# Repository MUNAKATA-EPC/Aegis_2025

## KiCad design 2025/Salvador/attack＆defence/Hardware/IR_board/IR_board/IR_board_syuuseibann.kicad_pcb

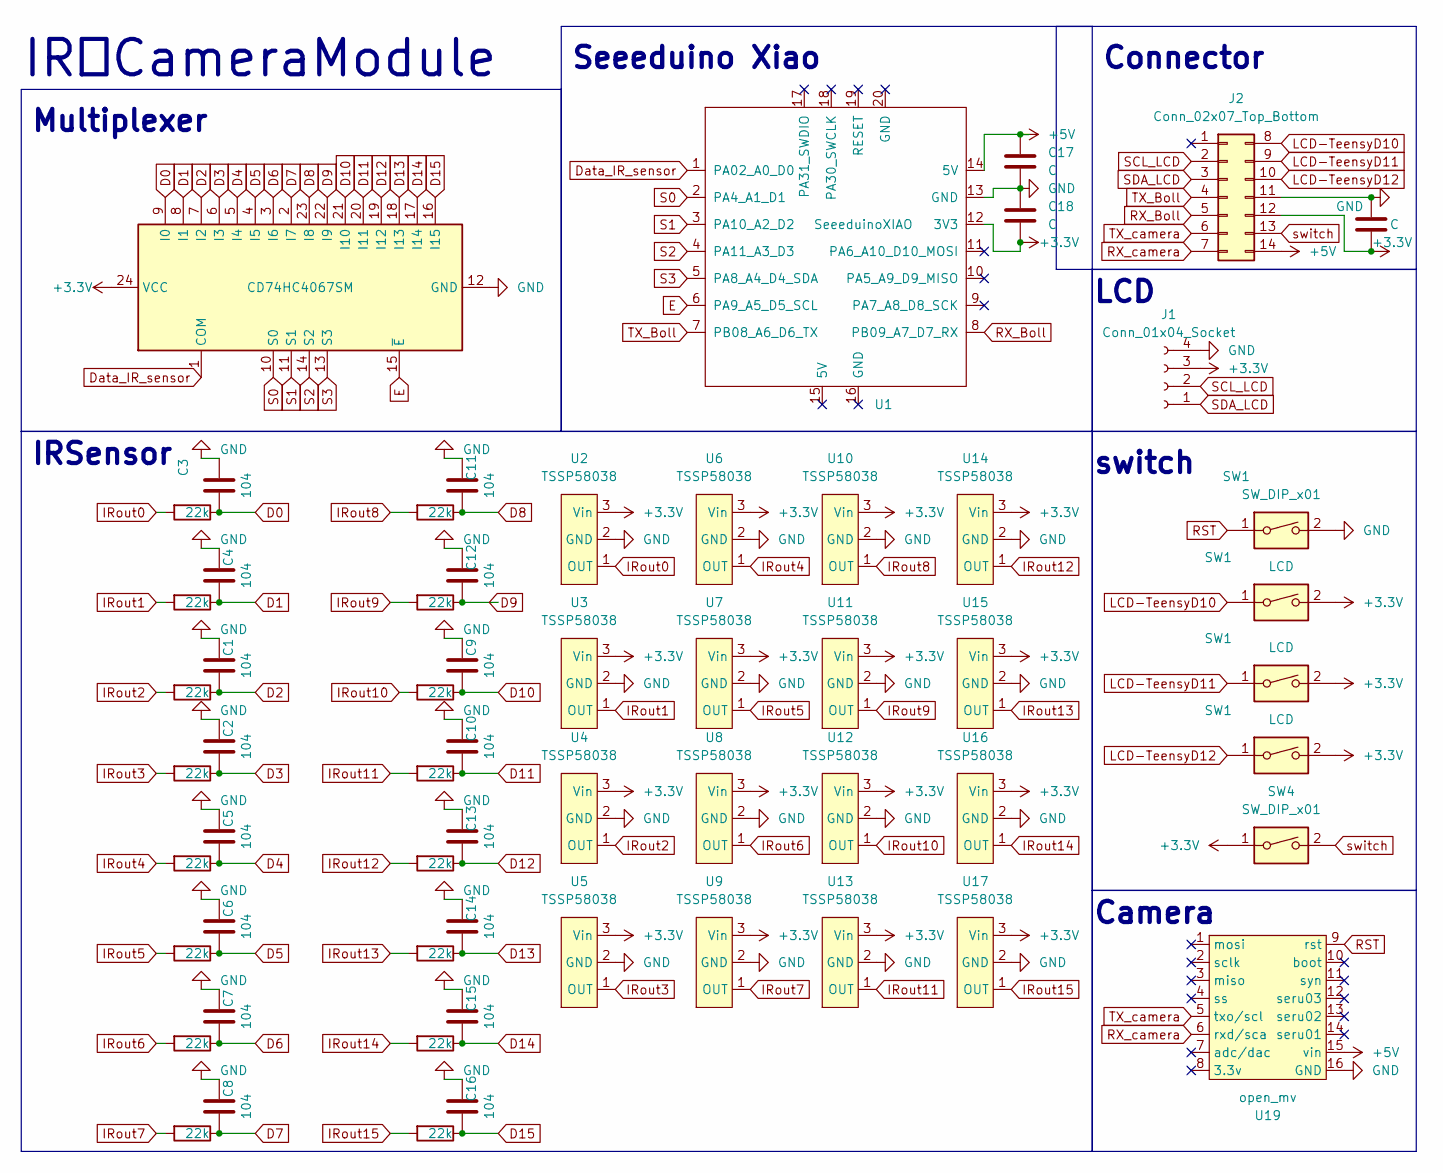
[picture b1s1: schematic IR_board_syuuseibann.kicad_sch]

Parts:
C1, C2, C3, C4, C5, C6, C7, C8, C9, C10, C11, C12, C13, C14, C15, C16: 104; C_Disc_D5.0mm_W2.5mm_P2.50mm
C17, C18, C19: C; C_Disc_D5.0mm_W2.5mm_P2.50mm
J1: Conn_01x04_Socket; PinHeader_1x04_P2.54mm_Vertical
J2: Conn_02x07_Top_Bottom; IDC-Header_2x07_P2.54mm_Vertical
R1, R2, R3, R4, R5, R6, R7, R8, R9, R10, R11, R12, R13, R14, R15, R16: 22k; R_Axial_DIN0204_L3.6mm_D1.6mm_P5.08mm_Vertical
SW1: LCD; SW_PUSH_6mm_H5mm
SW4: SW_DIP_x01; PinHeader_1x02_P2.54mm_Vertical
U1: SeeeduinoXIAO; seeeduinoXIAO
U2, U3, U4, U5, U6, U7, U8, U9, U10, U11, U12, U13, U14, U15, U16, U17: TSSP58038; PinHeader_1x03_P2.54mm_Vertical
U18: CD74HC4067SM; SSOP-24_5.3x8.2mm_P0.65mm
U19: open_mv; OpenMV

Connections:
+3.3V: C18.2, C19.2, J1.3, J2.12, SW1.2, SW4.1, U1.12 (3V3), U2.3 (Vin), U3.3 (Vin), U4.3 (Vin), U5.3 (Vin), U6.3 (Vin), U7.3 (Vin), U8.3 (Vin), U9.3 (Vin), U10.3 (Vin), U11.3 (Vin), U12.3 (Vin), U13.3 (Vin), U14.3 (Vin), U15.3 (Vin), U16.3 (Vin), U17.3 (Vin), U18.24 (VCC); also elsewhere on the board
+5V: C17.1, J2.14, U1.14 (5V), U19.15 (vin)
D0: C3.1, R3.1, U18.9 (I0)
D1: C4.1, R4.1, U18.8 (I1)
D2: C1.1, R1.1, U18.7 (I2)
D3: C2.1, R2.1, U18.6 (I3)
D4: C5.1, R5.1, U18.5 (I4)
D5: C6.1, R6.1, U18.4 (I5)
D6: C7.1, R7.1, U18.3 (I6)
D7: C8.1, R8.1, U18.2 (I7)
D8: C11.1, R11.1, U18.23 (I8)
D9: C12.1, R12.1, U18.22 (I9)
D10: C9.1, R9.1, U18.21 (I10)
D11: C10.1, R10.1, U18.20 (I11)
D12: C13.1, R13.1, U18.19 (I12)
D13: C14.1, R14.1, U18.18 (I13)
D14: C15.1, R15.1, U18.17 (I14)
D15: C16.1, R16.1, U18.16 (I15)
Data_IR_sensor: U1.1 (PA02_A0_D0), U18.1 (COM)
E: U1.6 (PA9_A5_D5_SCL), U18.15 (~E)
GND: C1.2, C2.2, C3.2, C4.2, C5.2, C6.2, C7.2, C8.2, C9.2, C10.2, C11.2, C12.2, C13.2, C14.2, C15.2, C16.2, C17.2, C18.1, C19.1, J1.4, J2.11, SW1.2, U1.13 (GND), U2.2 (GND), U3.2 (GND), U4.2 (GND), U5.2 (GND), U6.2 (GND), U7.2 (GND), U8.2 (GND), U9.2 (GND), U10.2 (GND), U11.2 (GND), U12.2 (GND), U13.2 (GND), U14.2 (GND), U15.2 (GND), U16.2 (GND), U17.2 (GND), U18.12 (GND), U19.16 (GND); also elsewhere on the board
IRout0: R3.2, U2.1 (OUT)
IRout1: R4.2, U3.1 (OUT)
IRout2: R1.2, U4.1 (OUT)
IRout3: R2.2, U5.1 (OUT)
IRout4: R5.2, U6.1 (OUT)
IRout5: R6.2, U7.1 (OUT)
IRout6: R7.2, U8.1 (OUT)
IRout7: R8.2, U9.1 (OUT)
IRout8: R11.2, U10.1 (OUT)
IRout9: R12.2, U11.1 (OUT)
IRout10: R9.2, U12.1 (OUT)
IRout11: R10.2, U13.1 (OUT)
IRout12: R13.2, U14.1 (OUT)
IRout13: R14.2, U15.1 (OUT)
IRout14: R15.2, U16.1 (OUT)
IRout15: R16.2, U17.1 (OUT)
LCD-TeensyD10: J2.8, SW1.1; also elsewhere on the board
LCD-TeensyD11: J2.9; also elsewhere on the board
LCD-TeensyD12: J2.10, SW1.1; also elsewhere on the board
RST: SW1.1, U19.9 (rst); also elsewhere on the board
RX_Boll: J2.5, U1.8 (PB09_A7_D7_RX)
RX_camera: J2.7, U19.6 (rxd/sca)
S0: U1.2 (PA4_A1_D1), U18.10 (S0)
S1: U1.3 (PA10_A2_D2), U18.11 (S1)
S2: U1.4 (PA11_A3_D3), U18.14 (S2)
S3: U1.5 (PA8_A4_D4_SDA), U18.13 (S3)
SCL_LCD: J1.2, J2.2
SDA_LCD: J1.1, J2.3
TX_Boll: J2.4, U1.7 (PB08_A6_D6_TX)
TX_camera: J2.6, U19.5 (txo/scl)
switch: J2.13, SW4.2

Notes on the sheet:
LCD
switch
Multiplexer
Camera
IRSensor
Connector
Seeeduino Xiao
IR＆CameraModule

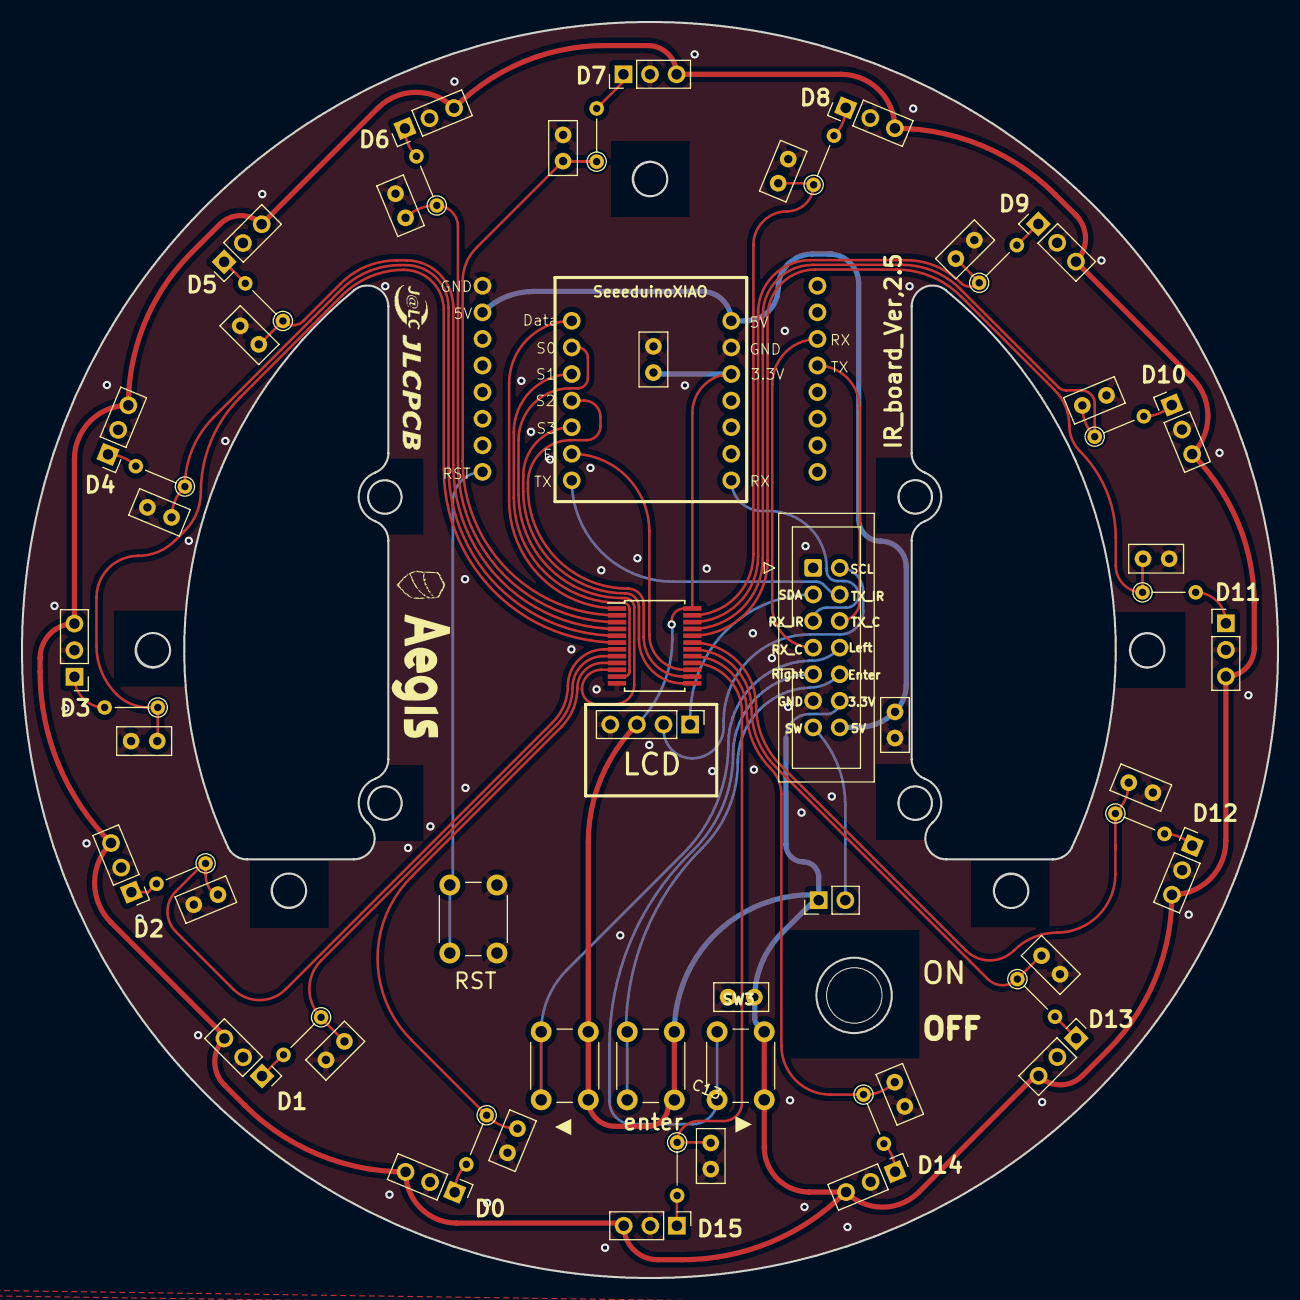
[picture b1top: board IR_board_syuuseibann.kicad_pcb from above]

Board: 2 copper layers, 120.0 x 120.0 mm, 61 parts (0 on the bottom side), 52 nets.

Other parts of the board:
RST: SW_DIP_x01; SW_PUSH_6mm_H5mm
SW3: LCD; SW_PUSH_6mm_H5mm
enter: LCD; SW_PUSH_6mm_H5mm
▶: LCD; SW_PUSH_6mm_H5mm

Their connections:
+3.3V: SW3.2, enter.2, ▶.2; also elsewhere on the board
GND: RST.2; also elsewhere on the board
LCD-TeensyD10: ▶.1; also elsewhere on the board
LCD-TeensyD11: SW3.1; also elsewhere on the board
LCD-TeensyD12: enter.1; also elsewhere on the board
RST: RST.1; also elsewhere on the board

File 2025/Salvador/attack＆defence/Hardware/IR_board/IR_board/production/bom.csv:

Designator,Footprint,Quantity,Value,LCSC Part #
"C1, C10, C11, C12, C13, C14, C15, C16, C2, C3, C4, C5, C6, C7, C8, C9",C_Disc_D5.0mm_W2.5mm_P2.50mm,16,104,
Camera_RST1,SW_PUSH_6mm_H5mm,1,SW_DIP_x01,
J1,PinHeader_1x04_P2.54mm_Vertical,1,Conn_01x04_Socket,
J2,IDC-Header_2x07_P2.54mm_Vertical,1,Conn_02x07_Top_Bottom,
"R1, R10, R11, R12, R13, R14, R15, R16, R2, R3, R4, R5, R6, R7, R8, R9",R_Axial_DIN0204_L3.6mm_D1.6mm_P5.08mm_Vertical,16,22k,
"SW1, SW2, SW3",SW_PUSH_6mm_H5mm,3,LCD,
SW4,PinHeader_1x02_P2.54mm_Vertical,1,SW_DIP_x01,
U1,seeeduinoXIAO,1,SeeeduinoXIAO,
"U10, U11, U12, U13, U14, U15, U16, U17, U2, U3, U4, U5, U6, U7, U8, U9",PinHeader_1x03_P2.54mm_Vertical,16,TSSP58038,
U18,SSOP-24_5.3x8.2mm_P0.65mm,1,CD74HC4067SM,
U19,OpenMV,1,open_mv,

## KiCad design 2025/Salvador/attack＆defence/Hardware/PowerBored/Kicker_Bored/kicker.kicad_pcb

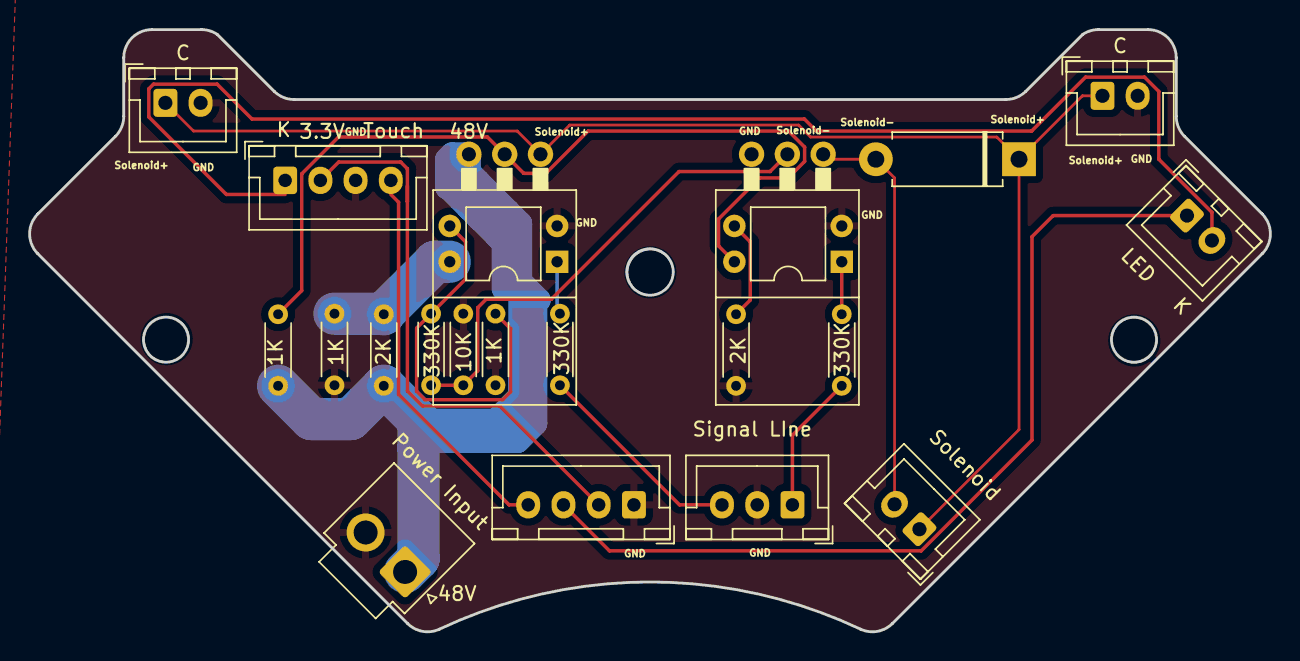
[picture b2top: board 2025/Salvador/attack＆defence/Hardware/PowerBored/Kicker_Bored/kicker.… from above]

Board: 2 copper layers, 88.1 x 42.7 mm, 22 parts (0 on the bottom side), 17 nets.

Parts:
1K, 1K#2: 1K; R_Axial_DIN0204_L3.6mm_D1.6mm_P5.08mm_Horizontal
2K, 2K#2: 2K; R_Axial_DIN0204_L3.6mm_D1.6mm_P5.08mm_Horizontal
330K, 330K#2: 330K; R_Axial_DIN0204_L3.6mm_D1.6mm_P5.08mm_Horizontal
C: C; JST_XH_B2B-XH-A_1x02_P2.50mm_Vertical
C#2: C; JST_XH_B2B-XH-A_1x02_P2.50mm_Vertical
D1: D; D_DO-15_P10.16mm_Horizontal
J1: Conn_01x02_Socket; JST_VH_B2P-VH_1x02_P3.96mm_Vertical
J2, J6: Conn_01x04_Socket; JST_XH_B4B-XH-A_1x04_P2.50mm_Vertical
J3: Conn_01x03_Socket; JST_XH_B3B-XH-A_1x03_P2.50mm_Vertical
J4, J5: Conn_01x02_Socket; JST_XH_B2B-XH-A_1x02_P2.50mm_Vertical
Q1: PMOS; K15A20D
Q3: NMOS; K15A20D
R3: 330K; R_Axial_DIN0204_L3.6mm_D1.6mm_P5.08mm_Horizontal
R4: 10K; R_Axial_DIN0204_L3.6mm_D1.6mm_P5.08mm_Horizontal
R5: １K; R_Axial_DIN0204_L3.6mm_D1.6mm_P5.08mm_Horizontal
U1, U2: EL817; DIP-4_W7.62mm

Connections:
+3.3V: J2.2, J6.2
+15V: 1K.1, 2K#2.2, U2.4
+48V: 1K#2.1, 2K#2.1, J1.1, Q1.3 (S)
FET1: 330K#2.1, J3.1
FET２: 330K.1, J3.3
GND: 1K.2, 2K.2, C.2, C#2.2, J1.2, J2.1, J3.2, J6.3, Q3.3 (S), R4.2, R5.2, U1.2, U2.2
K: J5.2, J6.1
LED: J2.3, J5.1
unnamed: 1K#2.2, Q1.2 (G), U1.4
unnamed: Q3.2 (G), R3.1, R4.1
unnamed: 330K#2.2, U1.1
unnamed: R3.2, R5.1, U2.3
unnamed: 2K.1, U1.3
unnamed: 330K.2, U2.1
Solenoid+: C.1, C#2.1, D1.1 (K), J4.1, Q1.1 (D)
Solenoid-: D1.2 (A), J4.2, Q3.1 (D)
Touch: J2.4, J6.4

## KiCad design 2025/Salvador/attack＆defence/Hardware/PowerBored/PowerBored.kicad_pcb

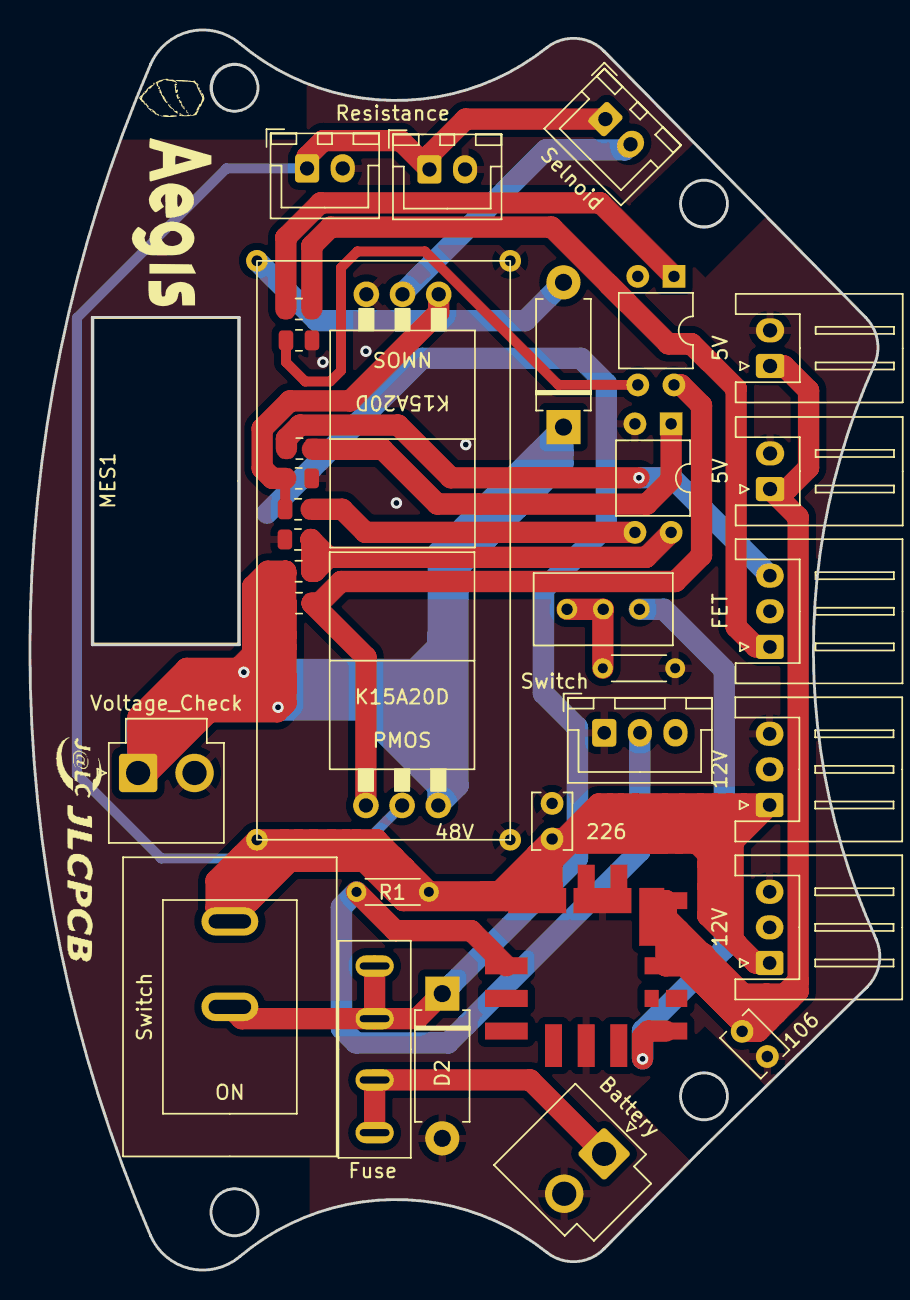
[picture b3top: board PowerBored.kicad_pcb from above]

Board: 2 copper layers, 59.7 x 87.1 mm, 35 parts (0 on the bottom side), 21 nets.

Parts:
5V, 5V#2: Conn_01x02_Socket; JST_XH_S2B-XH-A_1x02_P2.50mm_Horizontal
12V, 12V#2: Conn_01x03_Socket; JST_XH_S3B-XH-A_1x03_P2.50mm_Horizontal
106: C; C_Disc_D3.8mm_W2.6mm_P2.50mm
BT1: Battery; JST_VH_B2P-VH_1x02_P3.96mm_Vertical
C1: C; C_Disc_D3.8mm_W2.6mm_P2.50mm
C3, C4: C; JST_XH_B2B-XH-A_1x02_P2.50mm_Vertical
D1, D2: D; D_DO-15_P10.16mm_Horizontal
FET: Conn_01x03_Socket; JST_XH_S3B-XH-A_1x03_P2.50mm_Horizontal
Fuse: Fuse; fuse_socket
MES1: Voltmeter_DC; voltage_counter
Q1: PMOS; K15A20D
Q2: NMOS; K15A20D
R1, R2: R; R_Axial_DIN0204_L3.6mm_D1.6mm_P5.08mm_Horizontal
R3, R4, R7: 330; R_0805_2012Metric
R5, R9: 2K; R_0805_2012Metric
R6, R10: 1K; R_0805_2012Metric
R8: 10K; R_0805_2012Metric
RV1: R_Potentiometer_Trim_US; Potentiometer_Bourns_3296W_Vertical
Selnoid: Conn_01x02_Socket; JST_XH_B2B-XH-A_1x02_P2.50mm_Vertical
Switch: SW_DIP_x01; JST_XH_B3B-XH-A_1x03_P2.50mm_Vertical
Switch#2: SW_DIP_x01; DS-850k
U1: OKL-T_6-W12N-C; DCDC-murata-6A
U2: XL6009
U3, U4: EL817; DIP-4_W7.62mm
Voltage_Check: Conn_01x02_Socket; JST_VH_B2P-VH_1x02_P3.96mm_Vertical

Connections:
+5V: 5V.1, 5V#2.1, 106.1, U1.4 (VOUT), U1.5 (SENSE)
+12V: 12V.1, 12V#2.1, C1.1, R1.1, Switch#2.2, U1.2 (VIN), U2.1 (IN＋)
+15V: R9.2, R10.1, U4.4
+48V: D1.1 (K), Q1.3 (S), R6.1, R9.1, Voltage_Check.1
FET1: FET.1, R3.1
FET２: FET.3, R4.1
GND: 5V.2, 5V#2.2, 12V.3, 12V#2.3, 106.2, BT1.2 (-), C1.2, C3.2, C4.2, D2.2 (A), FET.2, MES1.1 (-), Q2.3 (S), R2.2, R5.2, R8.2, R10.2, Switch.1, U1.3 (GND), U1.7 (GND), U2.2 (IN－), U2.4 (OUT－), U3.2, U4.2, Voltage_Check.2
unnamed: BT1.1 (+), Fuse.1
unnamed: D1.2 (A), U2.3 (OUT＋)
unnamed: D2.1 (K), Fuse.2, MES1.2 (+), Switch#2.1
unnamed: Q1.2 (G), R6.2, U3.4
unnamed: Q2.2 (G), R7.1, R8.1
unnamed: R2.1, RV1.1, RV1.2
unnamed: R3.2, U3.1
unnamed: R4.2, U4.1
unnamed: R5.1, U3.3
unnamed: R7.2, U4.3
unnamed: R1.2, Switch.2, U1.1 (ON/OFF_CTRL)
unnamed: RV1.3, U1.6 (TRIM)
Solenoid+: C3.1, C4.1, Q1.1 (D), Selnoid.1
Solenoid-: Q2.1 (D), Selnoid.2

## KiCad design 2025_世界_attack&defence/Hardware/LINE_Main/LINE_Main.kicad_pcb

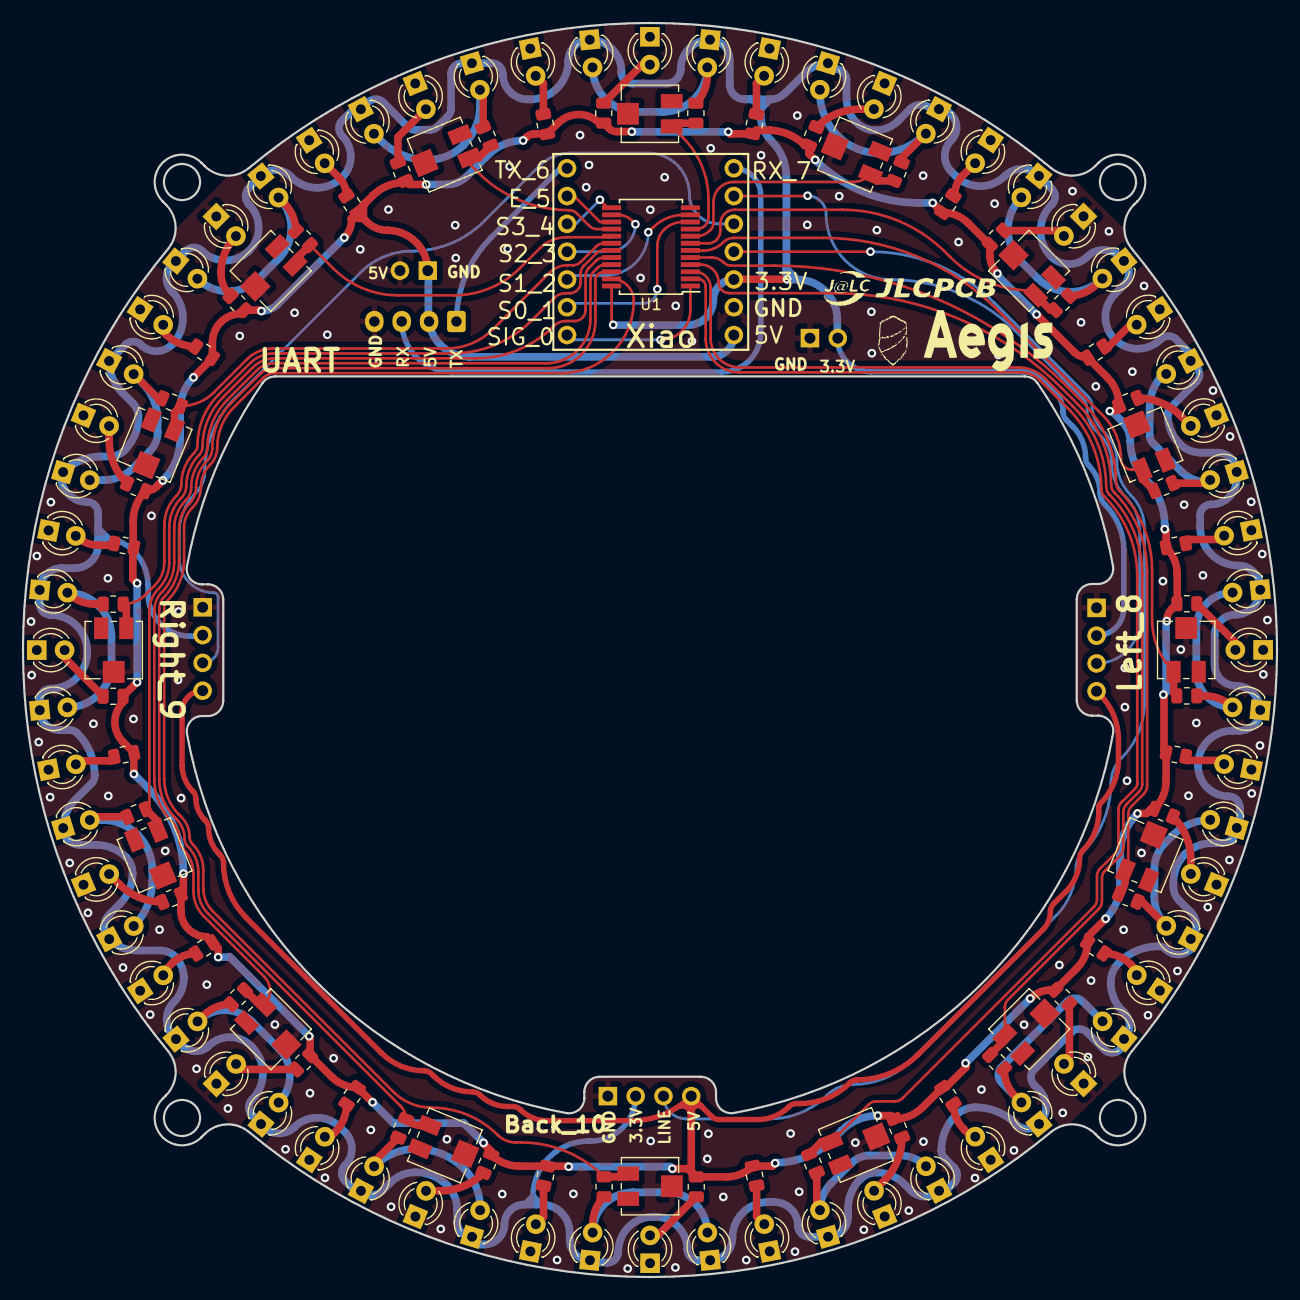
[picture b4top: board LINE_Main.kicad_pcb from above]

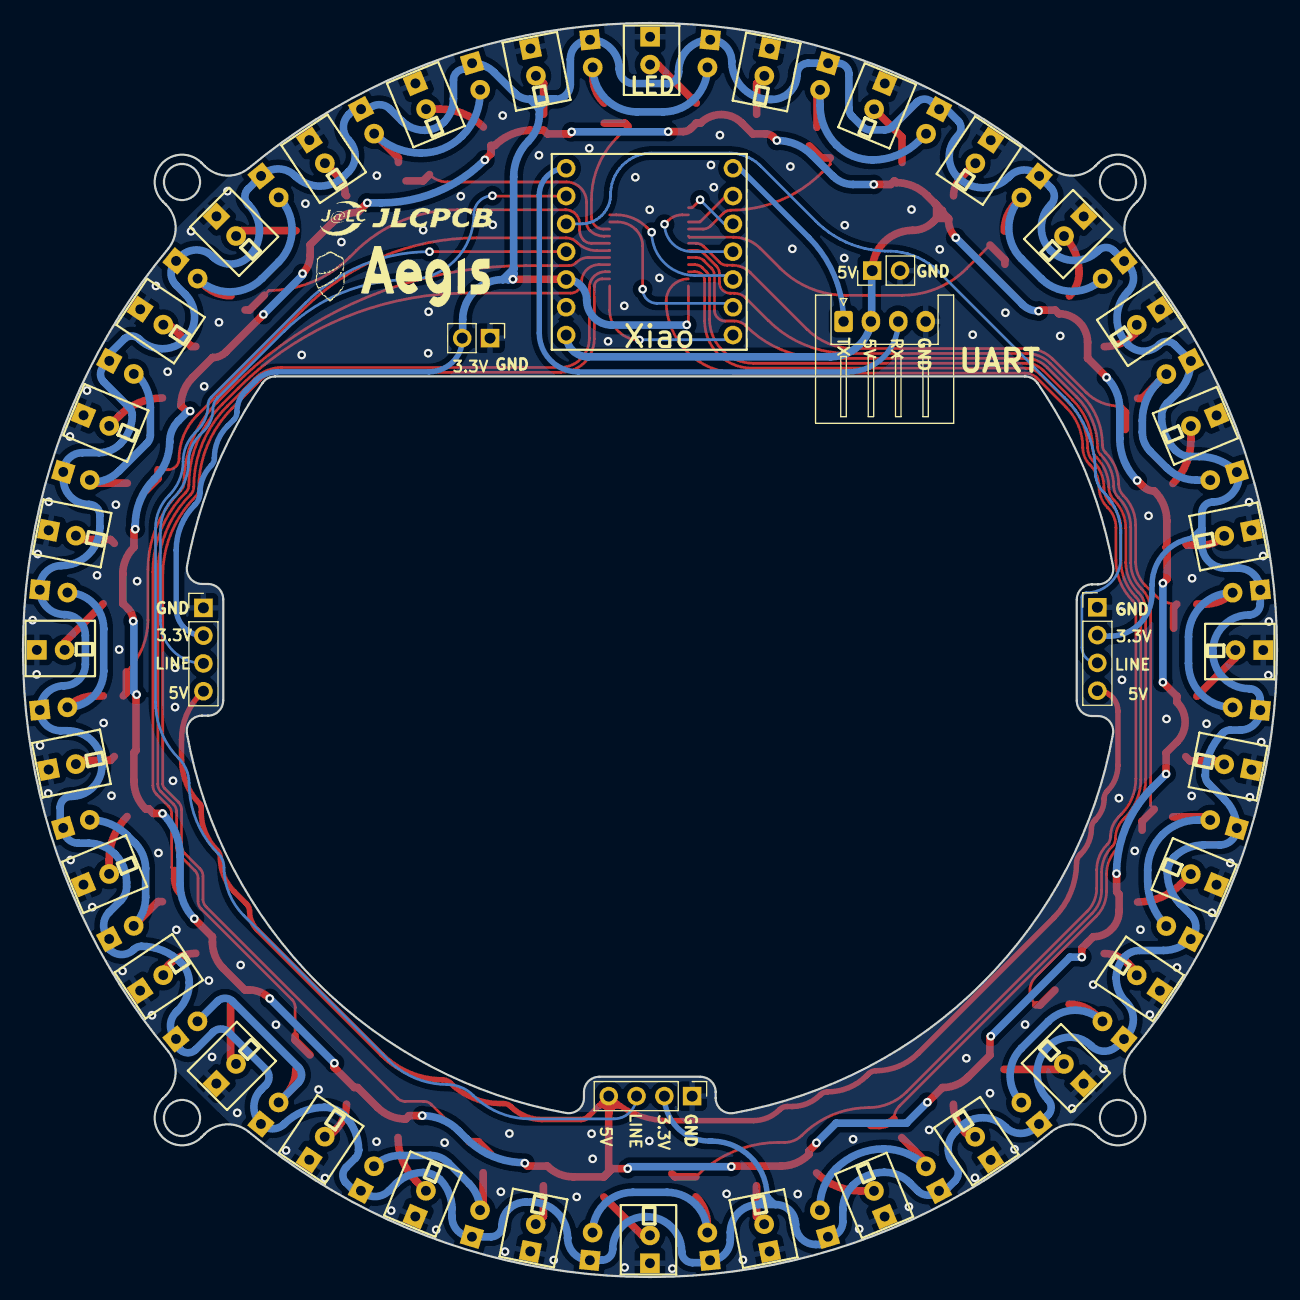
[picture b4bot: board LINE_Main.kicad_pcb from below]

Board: 2 copper layers, 114.6 x 114.6 mm, 136 parts (7 on the bottom side), 78 nets.

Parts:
C1, C2: C; PinHeader_1x02_P2.54mm_Vertical
D1, D2, D3, D4, D5, D6, D7, D8, D9, D10, D11, D12, D13, D14, D15, D16, D17, D18, D19, D20, D21, D22, D23, D24, D25, D26, D27, D28, D29, D30, D31, D32: LED; LED_D3.0mm_Clear
J1: Conn_01x04_Socket; JST_XH_S4B-XH-A_1x04_P2.50mm_Horizontal
J2, J3, J4: Conn_01x04_Socket; PinHeader_1x04_P2.54mm_Vertical
Q1, Q2, Q3, Q4, Q5, Q6, Q7, Q8, Q9, Q10, Q11, Q12, Q13, Q14, Q15, Q16, Q17, Q18, Q19, Q20, Q21, Q22, Q23, Q24, Q25, Q26, Q27, Q28, Q29, Q30, Q31, Q32: Q_Photo_NPN; LED_D3.0mm_Clear
R1, R2, R3, R4, R5, R6, R7, R8, R9, R10, R11, R12, R13, R14, R15, R16, R17, R18, R19, R20, R21, R22, R23, R24, R25, R26, R27, R28, R29, R30, R31, R32, R33, R34, R35, R36, R37, R38, R39, R40, R41, R42, R43, R44, R45, R46, R47, R48: R; R_0805_2012Metric
RV1, RV2, RV3, RV4, RV5, RV6, RV7, RV8, RV9, RV10, RV11, RV12, RV13, RV14, RV15, RV16: R_Potentiometer_Trim_US; Potentiometer_Vishay_TS53YJ_Vertical
U1: CD74HC4067SM; SSOP-24_5.3x8.2mm_P0.65mm
U2: Seeeduino_Xiao; seeeduinoXIAO

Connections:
1: R1.2, RV1.3, U1.9 (I0)
2: R2.2, RV2.3, U1.8 (I1)
3: R3.2, RV3.3, U1.7 (I2)
4: R4.2, RV4.3, U1.6 (I3)
5: R5.2, RV5.3, U1.5 (I4)
6: R6.2, RV6.3, U1.4 (I5)
7: R7.2, RV7.3, U1.3 (I6)
8: R8.2, RV8.3, U1.2 (I7)
9: R9.2, RV9.3, U1.23 (I8)
10: R10.2, RV10.3, U1.22 (I9)
11: R11.2, RV11.3, U1.21 (I10)
12: R12.2, RV12.3, U1.20 (I11)
13: R13.2, RV13.3, U1.19 (I12)
14: R14.2, RV14.3, U1.18 (I13)
15: R15.2, RV15.3, U1.17 (I14)
16: R16.2, RV16.3, U1.16 (I15)
+3.3V: C2.2, J2.2, J3.2, J4.2, Q1.1 (C), Q2.1 (C), Q3.1 (C), Q4.1 (C), Q5.1 (C), Q6.1 (C), Q7.1 (C), Q8.1 (C), Q9.1 (C), Q10.1 (C), Q11.1 (C), Q12.1 (C), Q13.1 (C), Q14.1 (C), Q15.1 (C), Q16.1 (C), Q17.1 (C), Q18.1 (C), Q19.1 (C), Q20.1 (C), Q21.1 (C), Q22.1 (C), Q23.1 (C), Q24.1 (C), Q25.1 (C), Q26.1 (C), Q27.1 (C), Q28.1 (C), Q29.1 (C), Q30.1 (C), Q31.1 (C), Q32.1 (C), U1.24 (VCC), U2.12 (3V3)
+5V: C1.1, J1.2, J2.4, J3.4, J4.4, R17.1, R18.1, R19.1, R20.1, R21.1, R22.1, R23.1, R24.1, R25.1, R26.1, R27.1, R28.1, R29.1, R30.1, R31.1, R32.1, R33.1, R34.1, R35.1, R36.1, R37.1, R38.1, R39.1, R40.1, R41.1, R42.1, R43.1, R44.1, R45.1, R46.1, R47.1, R48.1, U2.14 (5V)
Data_Line_sensor: U1.1 (COM), U2.1 (DAC)
E: U1.15 (~E), U2.6 (SCL)
GND: C1.2, C2.1, D1.1 (K), D2.1 (K), D3.1 (K), D4.1 (K), D5.1 (K), D6.1 (K), D7.1 (K), D8.1 (K), D9.1 (K), D10.1 (K), D11.1 (K), D12.1 (K), D13.1 (K), D14.1 (K), D15.1 (K), D16.1 (K), D17.1 (K), D18.1 (K), D19.1 (K), D20.1 (K), D21.1 (K), D22.1 (K), D23.1 (K), D24.1 (K), D25.1 (K), D26.1 (K), D27.1 (K), D28.1 (K), D29.1 (K), D30.1 (K), D31.1 (K), D32.1 (K), J1.4, J2.1, J3.1, J4.1, RV1.2, RV2.2, RV3.2, RV4.2, RV5.2, RV6.2, RV7.2, RV8.2, RV9.2, RV10.2, RV11.2, RV12.2, RV13.2, RV14.2, RV15.2, RV16.2, U1.12 (GND), U2.13 (GND)
Line_RX: J1.3, U2.8 (RX)
Line_TX: J1.1, U2.7 (TX)
unnamed: D1.2 (A), R17.2
unnamed: D2.2 (A), R18.2
unnamed: D3.2 (A), R19.2
unnamed: D4.2 (A), R20.2
unnamed: D5.2 (A), R21.2
unnamed: D6.2 (A), R22.2
unnamed: D7.2 (A), R23.2
unnamed: D8.2 (A), R24.2
unnamed: D9.2 (A), R25.2
unnamed: D10.2 (A), R26.2
unnamed: D11.2 (A), R27.2
unnamed: D12.2 (A), R28.2
unnamed: D13.2 (A), R29.2
unnamed: D14.2 (A), R30.2
unnamed: D15.2 (A), R31.2
unnamed: D16.2 (A), R32.2
unnamed: D17.2 (A), R33.2
unnamed: D18.2 (A), R34.2
unnamed: D19.2 (A), R35.2
unnamed: D20.2 (A), R36.2
unnamed: D21.2 (A), R37.2
unnamed: D22.2 (A), R38.2
unnamed: D23.2 (A), R39.2
unnamed: D24.2 (A), R40.2
unnamed: D25.2 (A), R41.2
unnamed: D26.2 (A), R42.2
unnamed: D27.2 (A), R43.2
unnamed: D28.2 (A), R44.2
unnamed: D29.2 (A), R45.2
unnamed: D30.2 (A), R46.2
unnamed: D31.2 (A), R47.2
unnamed: D32.2 (A), R48.2
unnamed: Q1.2 (E), Q2.2 (E), R1.1
unnamed: Q3.2 (E), Q4.2 (E), R2.1
unnamed: Q5.2 (E), Q6.2 (E), R3.1
unnamed: Q7.2 (E), Q8.2 (E), R4.1
unnamed: Q9.2 (E), Q10.2 (E), R5.1
unnamed: Q11.2 (E), Q12.2 (E), R6.1
unnamed: Q13.2 (E), Q14.2 (E), R7.1
unnamed: Q15.2 (E), Q16.2 (E), R8.1
unnamed: Q17.2 (E), Q18.2 (E), R9.1
unnamed: Q19.2 (E), Q20.2 (E), R10.1
unnamed: Q21.2 (E), Q22.2 (E), R11.1
unnamed: Q23.2 (E), Q24.2 (E), R12.1
unnamed: Q25.2 (E), Q26.2 (E), R13.1
unnamed: Q27.2 (E), Q28.2 (E), R14.1
unnamed: Q29.2 (E), Q30.2 (E), R15.1
unnamed: Q31.2 (E), Q32.2 (E), R16.1
S0: U1.10 (S0), U2.2
S1: U1.11 (S1), U2.3
S3: U1.14 (S2), U2.4
S4: U1.13 (S3), U2.5 (SDA)
Sensor_Back: J2.3, U2.11 (MOSI)
Sensor_Left: J4.3, U2.9 (SCK)
Sensor_Right: J3.3, U2.10 (MISO)

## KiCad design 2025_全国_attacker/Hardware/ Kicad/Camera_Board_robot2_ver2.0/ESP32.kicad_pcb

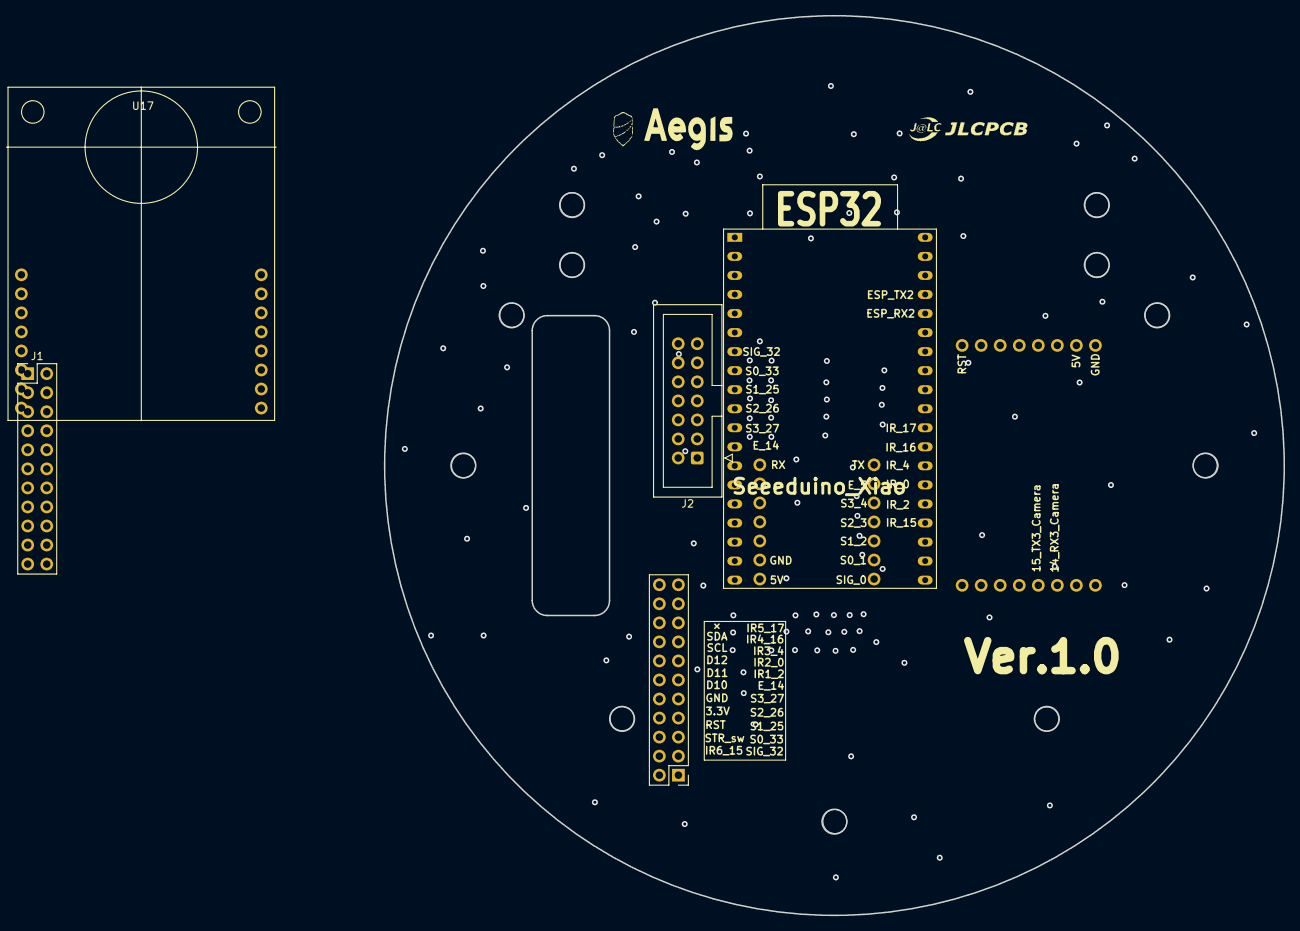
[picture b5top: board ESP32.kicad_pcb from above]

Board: 2 copper layers, 120.0 x 120.0 mm, 7 parts (0 on the bottom side), 26 nets, no tracks yet.

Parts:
ESP1: ESP32-DevKitC
J1, J1#2: Conn_02x11_Odd_Even; PinHeader_2x11_P2.54mm_Vertical
J2: Conn_02x07_Top_Bottom; IDC-Header_2x07_P2.54mm_Vertical
U2: Seeeduino_Xiao; seeeduinoXIAO
U17, U17#2: open_mv; OpenMV

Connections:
+3.3V: J1.8, J1#2.8, J2.12
+5V: ESP1.19 (5V), J2.14, U2.14 (5V), U17.15 (vin), U17#2.15 (vin)
Data_IR_sensor: ESP1.7 (32), J1.1, J1#2.1, U2.1 (DAC)
E: ESP1.12 (14), J1.11, J1#2.11, U2.6 (SCL)
GND: ESP1.14 (GND), ESP1.32 (GND), ESP1.38 (GND), J1.10, J1#2.10, J2.11, U2.13 (GND), U17.16 (GND), U17#2.16 (GND)
IR_Data1_Upside: ESP1.24 (2), J1.13, J1#2.13
IR_Data2_Upside: ESP1.25 (0), J1.15, J1#2.15
IR_Data3_Upside: ESP1.26 (4), J1.17, J1#2.17
IR_Data4_Upside: ESP1.29 (5), J1.19, J1#2.19
IR_Data5_Upside: ESP1.30 (18), J1.21, J1#2.21
IR_Data6_Upside: ESP1.23 (15), J1.2, J1#2.2
IR_board_RX: ESP1.27 (16), J2.5, U2.8 (RX)
IR_board_TX: ESP1.28 (17), J2.4, U2.7 (TX)
LCD-TeensyD10: J1.12, J1#2.12, J2.8
LCD-TeensyD11: J1.14, J1#2.14, J2.9
LCD-TeensyD12: J1.16, J1#2.16, J2.10
RST: J1.6, J1#2.6, U17.9 (rst), U17#2.9 (rst)
RX_camera: J2.7, U17.6 (rxd/sca), U17#2.6 (rxd/sca)
S0: ESP1.8 (33), J1.3, J1#2.3, U2.2
S1: ESP1.9 (25), J1.5, J1#2.5, U2.3
S2: ESP1.10 (26), J1.7, J1#2.7, U2.4
S3: ESP1.11 (27), J1.9, J1#2.9, U2.5 (SDA)
SCL_LCD: J1.18, J1#2.18, J2.2
SDA_LCD: J1.20, J1#2.20, J2.3
Start_switch: J1.4, J1#2.4, J2.13
TX_camera: J2.6, U17.5 (txo/scl), U17#2.5 (txo/scl)
